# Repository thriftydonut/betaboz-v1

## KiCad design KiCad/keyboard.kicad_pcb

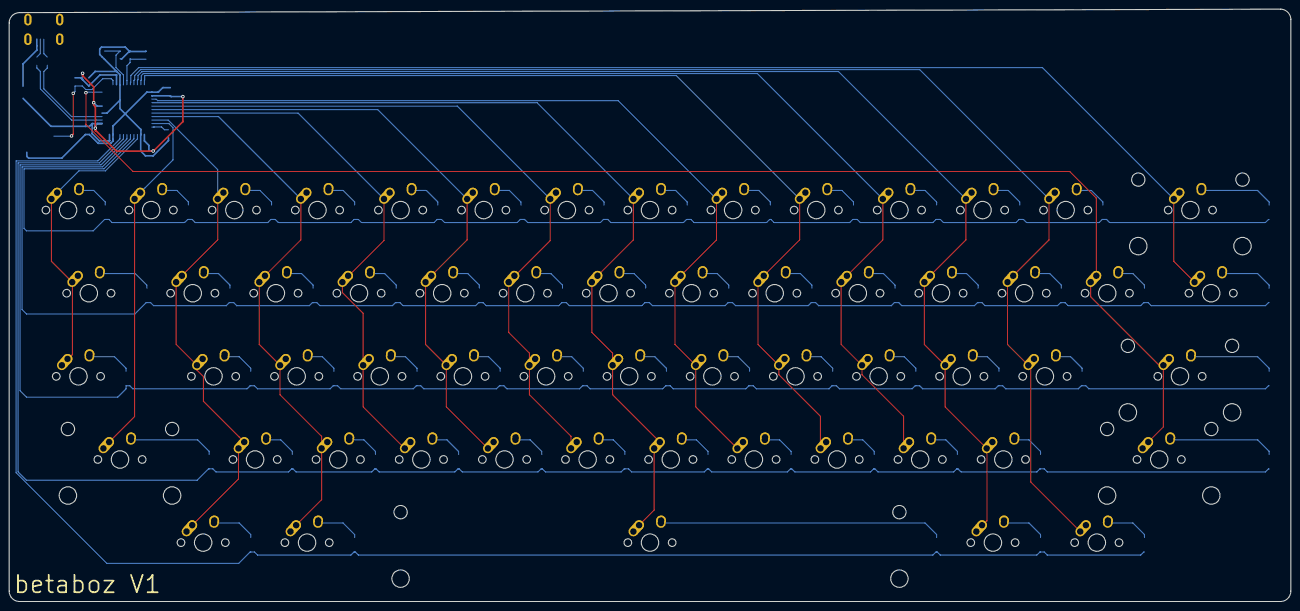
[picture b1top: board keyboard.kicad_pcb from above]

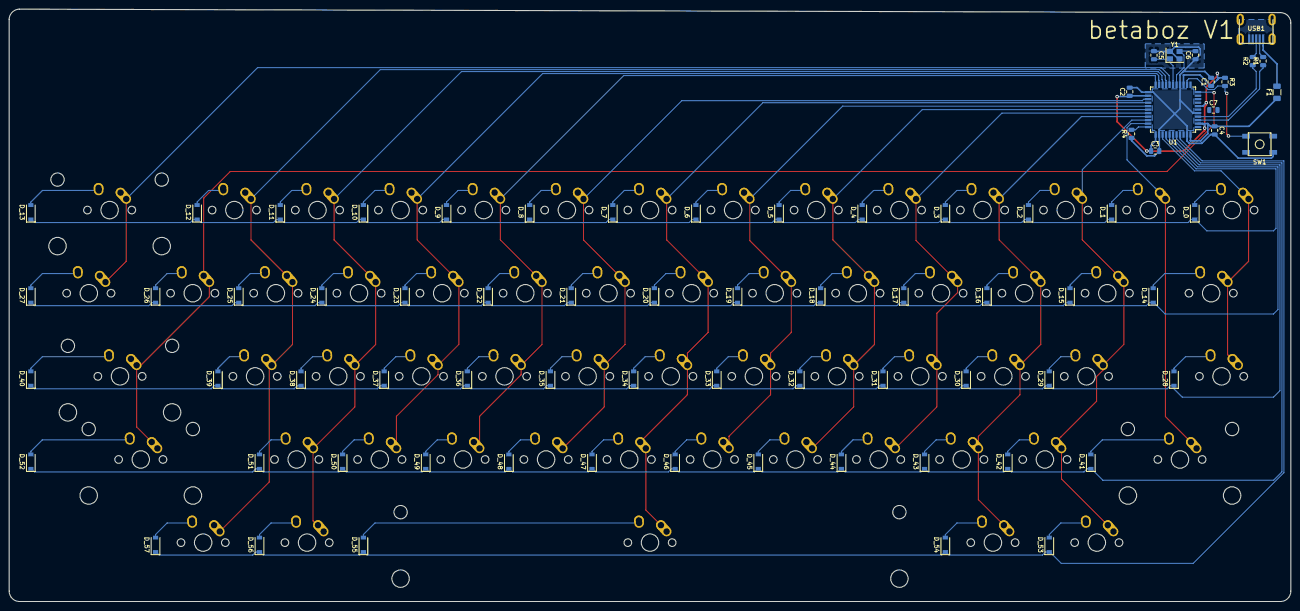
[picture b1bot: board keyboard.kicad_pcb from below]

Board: 2 copper layers, 293.7 x 135.7 mm, 132 parts (74 on the bottom side), 90 nets.

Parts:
C1, C2, C3: 0.1uF; C_0805_2012Metric
C4: 10uF; C_0805_2012Metric
C5, C6: 22pF; C_0805_2012Metric
C7: 1uF; C_0805_2012Metric
D_0, D_1, D_2, D_3, D_4, D_5, D_6, D_7, D_8, D_9, D_10, D_11, D_12, D_13, D_14, D_15, D_16, D_17, D_18, D_19, D_20, D_21, D_22, D_23, D_24, D_25, D_26, D_27, D_28, D_29, D_30, D_31, D_32, D_33, D_34, D_35, D_36, D_37, D_38, D_39, D_40, D_41, D_42, D_43, D_44, D_45, D_46, D_47, D_48, D_49, D_50, D_51, D_52, D_53, D_54, D_55, D_56, D_57: D; D_SOD-123
F1: Polyfuse; Fuse_1206_3216Metric
K_0, K_1, K_2, K_3, K_4, K_5, K_6, K_7, K_8, K_9, K_10, K_11, K_12, K_15, K_16, K_17, K_18, K_19, K_20, K_21, K_22, K_23, K_24, K_25, K_26, K_29, K_30, K_31, K_32, K_33, K_34, K_35, K_36, K_37, K_38, K_39, K_42, K_43, K_44, K_45, K_46, K_47, K_48, K_49, K_50, K_51: KEYSW; MX-1U-NoLED
K_13: KEYSW; MX-2U-NoLED
K_14, K_27: KEYSW; MX-1.5U-NoLED
K_28, K_53, K_54, K_56, K_57: KEYSW; MX-1.25U-NoLED
K_40, K_41: KEYSW; MX-2.25U-NoLED
K_52: KEYSW; MX-2.75U-NoLED
K_55: KEYSW; MX-7U-NoLED
R1, R2: 22; R_0805_2012Metric
R3: R_Small; R_0805_2012Metric
R4: 10k; R_0805_2012Metric
SW1: SW_Push; SKQG-1155865
U1: ATmega32U4-AU; TQFP-44_10x10mm_P0.8mm
USB1: Molex-0548190589
Y1: Crystal_GND24_Small; Crystal_SMD_3225-4Pin_3.2x2.5mm

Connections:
+5V: C1.1, C2.1, C3.1, C4.1, F1.1, R3.1, U1.2, U1.7, U1.14, U1.24, U1.34, U1.44
D+: R2.2, USB1.3
D-: R1.2, USB1.4
GND: C1.2, C2.2, C3.2, C4.2, C5.1, C6.1, C7.2, R4.1, SW1.1, U1.5, U1.15, U1.23, U1.35, U1.43, USB1.1, Y1.2, Y1.4
unnamed: C5.2, U1.17, Y1.1
unnamed: C6.2, U1.16, Y1.3
unnamed: C7.1, U1.6
unnamed: D_0.2, K_0.2
unnamed: D_1.2, K_1.2
unnamed: D_2.2, K_2.2
unnamed: D_3.2, K_3.2
unnamed: D_4.2, K_4.2
unnamed: D_5.2, K_5.2
unnamed: D_6.2, K_6.2
unnamed: D_7.2, K_7.2
unnamed: D_8.2, K_8.2
unnamed: D_9.2, K_9.2
unnamed: D_10.2, K_10.2
unnamed: D_11.2, K_11.2
unnamed: D_12.2, K_12.2
unnamed: D_13.2, K_13.2
unnamed: D_14.2, K_14.2
unnamed: D_15.2, K_15.2
unnamed: D_16.2, K_16.2
unnamed: D_17.2, K_17.2
unnamed: D_18.2, K_18.2
unnamed: D_19.2, K_19.2
unnamed: D_20.2, K_20.2
unnamed: D_21.2, K_21.2
unnamed: D_22.2, K_22.2
unnamed: D_23.2, K_23.2
unnamed: D_24.2, K_24.2
unnamed: D_25.2, K_25.2
unnamed: D_26.2, K_26.2
unnamed: D_27.2, K_27.2
unnamed: D_28.2, K_28.2
unnamed: D_29.2, K_29.2
unnamed: D_30.2, K_30.2
unnamed: D_31.2, K_31.2
unnamed: D_32.2, K_32.2
unnamed: D_33.2, K_33.2
unnamed: D_34.2, K_34.2
unnamed: D_35.2, K_35.2
unnamed: D_36.2, K_36.2
unnamed: D_37.2, K_37.2
unnamed: D_38.2, K_38.2
unnamed: D_39.2, K_39.2
unnamed: D_40.2, K_40.2
unnamed: D_41.2, K_41.2
unnamed: D_42.2, K_42.2
unnamed: D_43.2, K_43.2
unnamed: D_44.2, K_44.2
unnamed: D_45.2, K_45.2
unnamed: D_46.2, K_46.2
unnamed: D_47.2, K_47.2
unnamed: D_48.2, K_48.2
unnamed: D_49.2, K_49.2
unnamed: D_50.2, K_50.2
unnamed: D_51.2, K_51.2
unnamed: D_52.2, K_52.2
unnamed: D_53.2, K_53.2
unnamed: D_54.2, K_54.2
unnamed: D_55.2, K_55.2
unnamed: D_56.2, K_56.2
unnamed: D_57.2, K_57.2
unnamed: R1.1, U1.3
unnamed: R2.1, U1.4
unnamed: R3.2, SW1.2, U1.13
unnamed: R4.2, U1.33
VCC: F1.2, USB1.5
col0: K_0.1, K_14.1, K_28.1, U1.36
col1: K_1.1, K_41.1, U1.32
col2: K_2.1, K_15.1, K_29.1, K_42.1, K_53.1, U1.31
col3: K_3.1, K_16.1, K_30.1, K_43.1, K_54.1, U1.30
col4: K_4.1, K_17.1, K_31.1, K_44.1, U1.29
col5: K_5.1, K_18.1, K_32.1, K_45.1, U1.28
col6: K_6.1, K_19.1, K_33.1, K_46.1, U1.27
col7: K_7.1, K_20.1, K_34.1, K_47.1, K_55.1, U1.26
col8: K_8.1, K_21.1, K_35.1, K_48.1, U1.25
col9: K_9.1, K_22.1, K_36.1, K_49.1, U1.22
col10: K_10.1, K_23.1, K_37.1, K_50.1, U1.21
col11: K_11.1, K_24.1, K_38.1, K_51.1, K_56.1, U1.20
col12: K_12.1, K_25.1, K_39.1, K_57.1, U1.19
col13: K_26.1, K_40.1, K_52.1, U1.11
col14: K_13.1, K_27.1, U1.18
row0: D_0.1, D_1.1, D_2.1, D_3.1, D_4.1, D_5.1, D_6.1, D_7.1, D_8.1, D_9.1, D_10.1, D_11.1, D_12.1, D_13.1, U1.37
row1: D_14.1, D_15.1, D_16.1, D_17.1, D_18.1, D_19.1, D_20.1, D_21.1, D_22.1, D_23.1, D_24.1, D_25.1, D_26.1, D_27.1, U1.38
row2: D_28.1, D_29.1, D_30.1, D_31.1, D_32.1, D_33.1, D_34.1, D_35.1, D_36.1, D_37.1, D_38.1, D_39.1, D_40.1, U1.39
row3: D_41.1, D_42.1, D_43.1, D_44.1, D_45.1, D_46.1, D_47.1, D_48.1, D_49.1, D_50.1, D_51.1, D_52.1, U1.40
row4: D_53.1, D_54.1, D_55.1, D_56.1, D_57.1, U1.41

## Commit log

2021-08-06 Added SwillKB files and KLE link
2021-08-06 Downloaded PCB starting point from kb.xyz.is
    I would do the work setting up the switch matrix myself, it actually seems kinda fun, but... :P
2021-08-06 Added submodules
2021-08-06 Added footprint libraries
2021-08-06 Wired the MCU
2021-08-06 Wired USB
2021-08-06 Assigned footprints
2021-08-06 Components laid out
2021-08-06 Component placement tweaked
2021-08-06 Routed traces (except for switch matrix)
2021-08-06 Finished routing switch matrix
    ...I think :P
2021-08-06 Finalized PCB
2021-08-06 Generated Gerber files
2021-08-06 Updated PCB and Gerber files
2021-08-06 Changed directories around and added .svg of PCB
2021-08-06 Added previews
2021-08-06 Moved Gerber files to a .zip
2021-08-07 Removed SwillKB files
    They were kinda messy anyway, with the USB not lining up and some other things that I'd rather not fix right now :P
    I'd also kinda like to try designing my own case, which oyu can also do given there's still the .svg for the PCB
